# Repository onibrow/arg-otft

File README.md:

# Arias Research Group - Characterization of Organic Thin Film Transistors

### Seiya Ono Spring '19

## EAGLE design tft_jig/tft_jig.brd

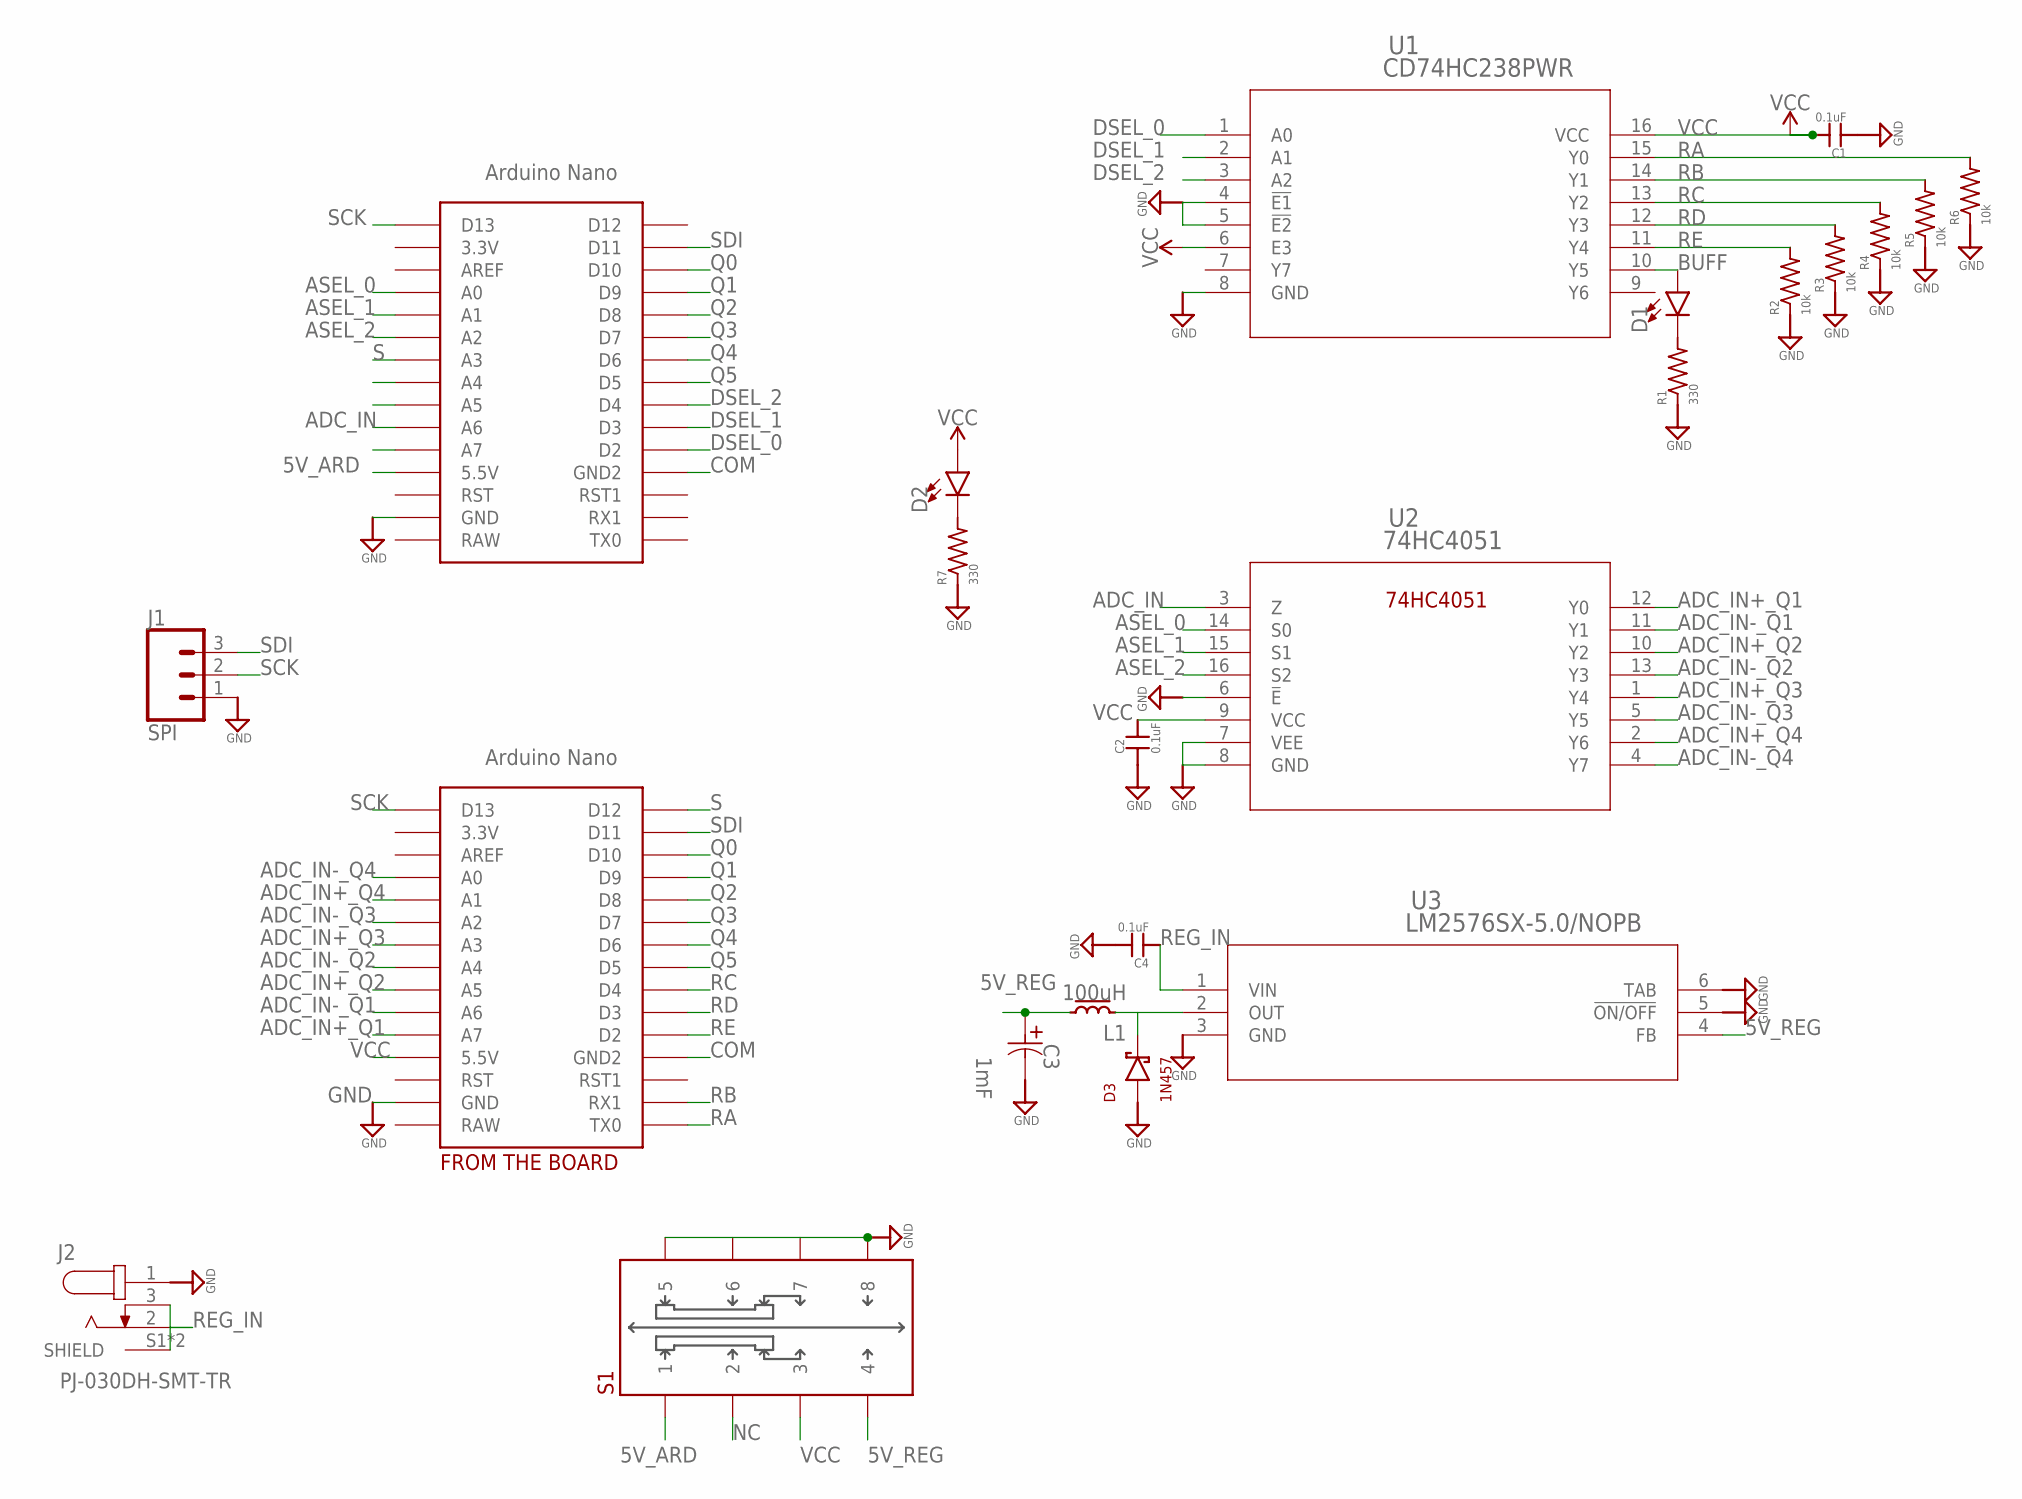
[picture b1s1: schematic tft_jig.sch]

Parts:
C1, C2, C4: 0.1uF; 0603-CAP
C3: 1mF; PCAP_8X10-ELECT
D1, D2: LED0603; LED-0603
D3: 1N457; DIODE_THRU
J1: SPI; 1X03
J2: PJ-030DH-SMT-TR; CUI_PJ-030DH-SMT-TR
L1: 100uH; IND_2012
R1, R7: 330; R0603
R2, R3, R4, R5, R6: 10k; R0603
S1: DP3T
U1: CD74HC238PWR; PW16
U2: 74HC4051; PW16
U3: LM2576SX-5.0/NOPB; TS5B
U$1, U$2: NANO

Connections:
5V_ARD: S1.1, U$1.5V (5.5V)
5V_REG: C3.1, L1.1, S1.4, U3.4 (FB)
ADC_IN: U2.3 (Z), U$1.A6
ADC_IN+_Q1: U2.12 (Y0), U$2.A7
ADC_IN+_Q2: U2.10 (Y2), U$2.A5
ADC_IN+_Q3: U2.1 (Y4), U$2.A3
ADC_IN+_Q4: U2.2 (Y6), U$2.A1
ADC_IN-_Q1: U2.11 (Y1), U$2.A6
ADC_IN-_Q2: U2.13 (Y3), U$2.A4
ADC_IN-_Q3: U2.5 (Y5), U$2.A2
ADC_IN-_Q4: U2.4 (Y7), U$2.A0
ASEL_0: U2.14 (S0), U$1.A0
ASEL_1: U2.15 (S1), U$1.A1
ASEL_2: U2.16 (S2), U$1.A2
BUFF: D1.A, U1.10 (Y5)
COM: U$1.GND1 (GND2), U$2.GND1 (GND2)
DSEL_0: U1.1 (A0), U$1.D2
DSEL_1: U1.2 (A1), U$1.D3
DSEL_2: U1.3 (A2), U$1.D4
GND: C1.1, C2.1, C3.2, C4.2, D3.1, J1.1, J2.1, R1.1, R2.1, R3.1, R4.1, R5.1, R6.1, R7.1, S1.5, S1.6, S1.7, S1.8, U1.4 (!E1), U1.5 (!E2), U1.8 (GND), U2.6 (!E), U2.7 (VEE), U2.8 (GND), U3.3 (GND), U3.5 (!ON/OFF), U3.6 (TAB), U$1.GND, U$2.GND
unnamed: D2.C, R7.2
unnamed: D3.2 (N), L1.2, U3.2 (OUT)
unnamed: D1.C, R1.2
NC: S1.2
Q0: U$1.D10, U$2.D10
Q1: U$1.D9, U$2.D9
Q2: U$1.D8, U$2.D8
Q3: U$1.D7, U$2.D7
Q4: U$1.D6, U$2.D6
Q5: U$1.D5, U$2.D5
RA: R6.2, U1.15 (Y0), U$2.TX0
RB: R5.2, U1.14 (Y1), U$2.RX1
RC: R4.2, U1.13 (Y2), U$2.D4
RD: R3.2, U1.12 (Y3), U$2.D3
RE: R2.2, U1.11 (Y4), U$2.D2
REG_IN: C4.1, J2.2, J2.3, J2.S1 (SHIELD), J2.S2 (SHIELD), U3.1 (VIN)
S: U$1.A3, U$2.D12
SCK: J1.2, U$1.D13, U$2.D13
SDI: J1.3, U$1.D11, U$2.D11
VCC: C1.2, C2.2, D2.A, S1.3, U1.6 (E3), U1.16 (VCC), U2.9 (VCC), U$2.5V (5.5V)

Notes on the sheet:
FROM THE BOARD

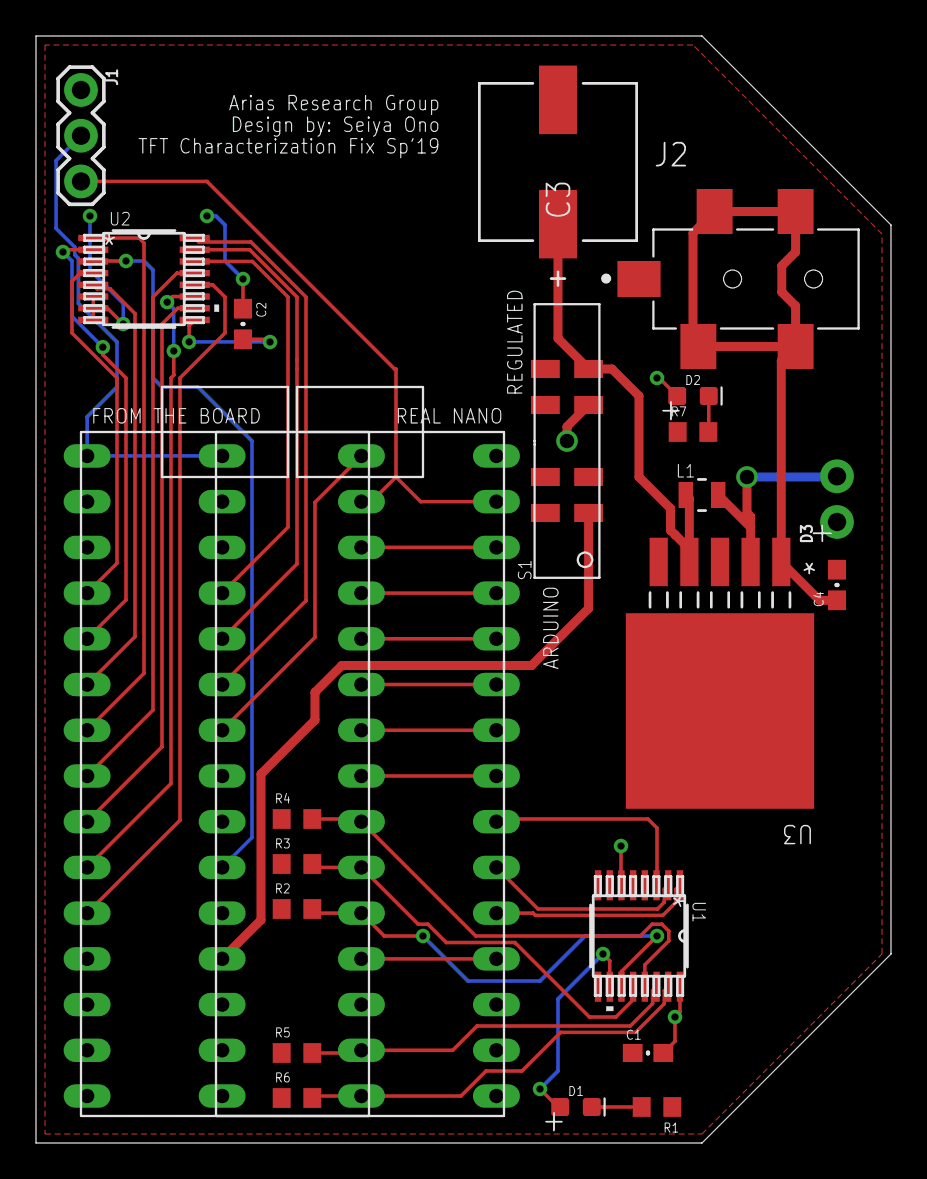
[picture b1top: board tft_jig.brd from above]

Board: 2 copper layers, 47.5 x 61.5 mm, 23 parts (0 on the bottom side), 39 nets.

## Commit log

2019-02-13 initialize repo
2019-02-13 import jan 23 data
2019-02-13 start parsing the data
2019-04-10 start pot code
2019-04-12 add bom and finalize board
2019-04-12 fix vcc cap
2019-04-12 add new gerb
2019-04-24 fix indexing
2019-04-24 import mahsas code
2019-04-25 finish coms and sweeps
2019-05-11 fix addressing code
2019-05-11 fix addressing
